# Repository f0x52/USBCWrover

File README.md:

# USBCWrover
Simple ESP32 board with USB C-serial and the Wrover module. It also supports the Wroom, at the expense of a few IO (but you gain IO16/17). Currently it's untested!

License: TBD

Art by @Ankhaneko from @tilde.industries

![board image][herofront]

[herofront]: https://github.com/sebastius/USBCWrover/blob/master/USBCWrover/documentation/hero_render.png "test"

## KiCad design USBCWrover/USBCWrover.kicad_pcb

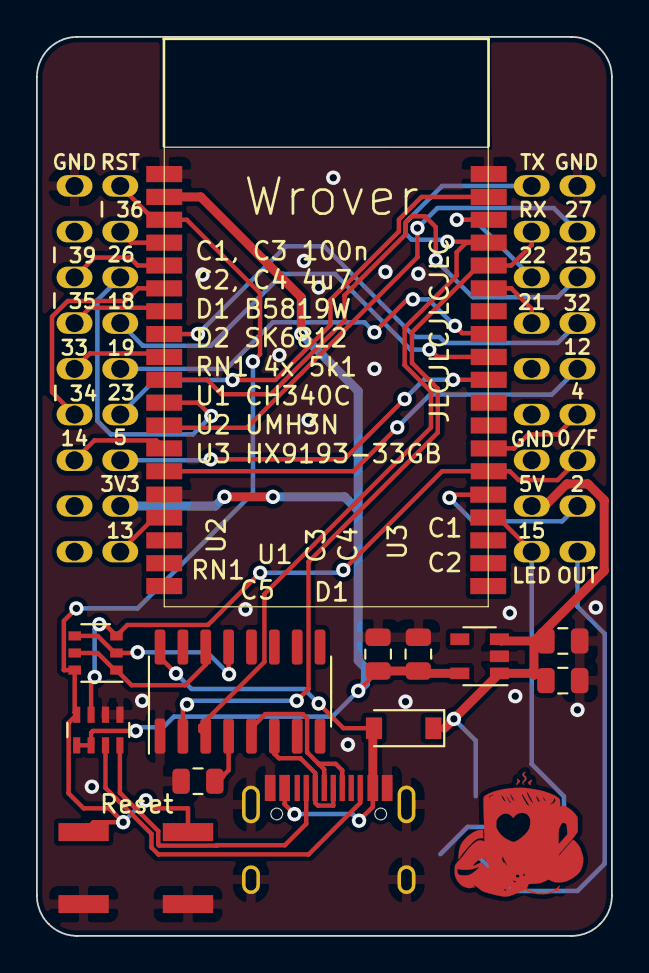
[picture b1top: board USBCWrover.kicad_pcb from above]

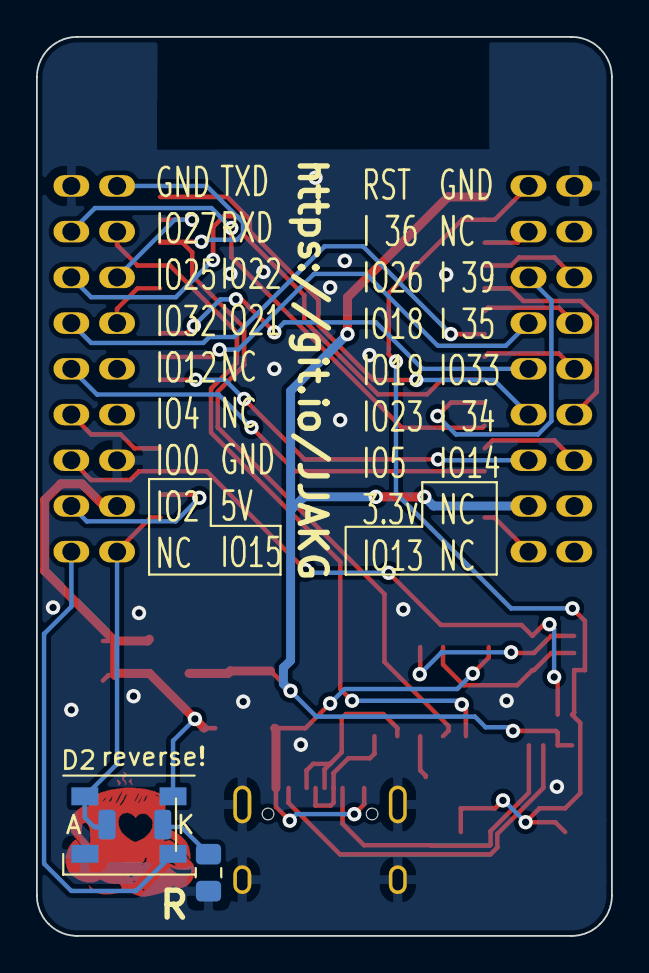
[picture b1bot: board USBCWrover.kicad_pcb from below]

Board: 2 copper layers, 31.9 x 49.9 mm, 18 parts (4 on the bottom side), 38 nets.

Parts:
C1, C4: 4u7; C_0805_2012Metric
C2, C3, C5: 100nF; C_0805_2012Metric
D1: b5819w; D_SOD-123
D2: SK6812; LED_SK6812_PLCC4_5.0x5.0mm_P3.2mm
D3: LED; LED_1206_3216Metric_ReverseMount_Hole1.8x2.4mm
J1: USB_C_Receptacle_USB2.0; USB_C_Receptacle_HRO_TYPE-C-31-M-12
J2, J3: Conn_02x10_Odd_Even; PinHeader_2x09_P2.54mm_Vertical
R1: R; R_0805_2012Metric_Pad1.15x1.40mm_HandSolder
RN1: R_Pack04; R_Array_Concave_4x0603
SW1: SW_Push; SW_Push_1P1T_NO_CK_KSC6xxJ
U1: CH340C; SOIC-16_3.9x9.9mm_P1.27mm
U2: UMH3N; TSOP-6_1.65x3.05mm_P0.95mm
U3: HX9193-33GB; SOT-23-5
U4: ESP32-WROVER

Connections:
+3V3: C3.1, C4.1, J3.15, RN1.1, RN1.2, U3.5, U4.2
+5V: C1.1, C2.1, D1.1, D2.3, J2.16, U3.1, U3.3
CC1: J1.A5, RN1.4
CC2: J1.B5, RN1.3
ESP_FLS: J2.13, RN1.7, U2.3, U4.25
ESP_RST: J3.1, RN1.8, SW1.1, U2.6, U4.3
ESP_RXD: J2.4, U1.2, U4.34
ESP_TXD: J2.2, U1.3, U4.35
GND: C1.2, C2.2, C3.2, C4.2, C5.1, D2.1, J1.A1, J1.A12, J1.B1, J1.B12, J1.S1, J2.1, J2.14, J3.2, R1.1, RN1.5, RN1.6, SW1.2, U1.1, U3.2, U4.1, U4.15, U4.38
IO2: J2.15, U4.24
IO4: J2.11, U4.26
IO5: J3.13, U4.29
IO12: J2.9, U4.14
IO13: J3.17, U4.16
IO14: J3.14, U4.13
IO15: D2.2, D3.2, J2.18, U4.23
IO18: J3.7, U4.30
IO19: J3.9, U4.31
IO21: J2.8, U4.33
IO22: J2.6, U4.36
IO23: J3.11, U4.37
IO25: J2.5, U4.10
IO26: J3.5, U4.11
IO27: J2.3, U4.12
IO32: J2.7, U4.8
IO33: J3.10, U4.9
IO34: J3.12, U4.6
IO35: J3.8, U4.7
unnamed: C5.2, U1.4
unnamed: D2.4, J2.17
unnamed: D3.1, R1.2
SENSOR_VN: J3.6, U4.5
SER_DTR: U1.13, U2.2, U2.4
SER_RTS: U1.14, U2.1, U2.5
Sensor_VP: J3.3, U4.4
USB_D+: J1.A6, J1.B6, U1.5
USB_D-: J1.A7, J1.B7, U1.6
VUSB: D1.2, J1.A4, J1.A9, J1.B4, J1.B9, U1.16

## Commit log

2020-08-19 not sure why its not working on my machine
2020-08-19 tried on linux, added footprints
2020-08-19 routing done, but not pretty
2020-08-19 added silkscreen back
2020-08-20 lot prettier
2020-08-20 gerbers
2020-08-20 now with art
2020-08-30 rework
2020-08-31 pads with text on top, resistor network instead of 4 resistors, usb serial rerouted
2020-09-06 redesign
